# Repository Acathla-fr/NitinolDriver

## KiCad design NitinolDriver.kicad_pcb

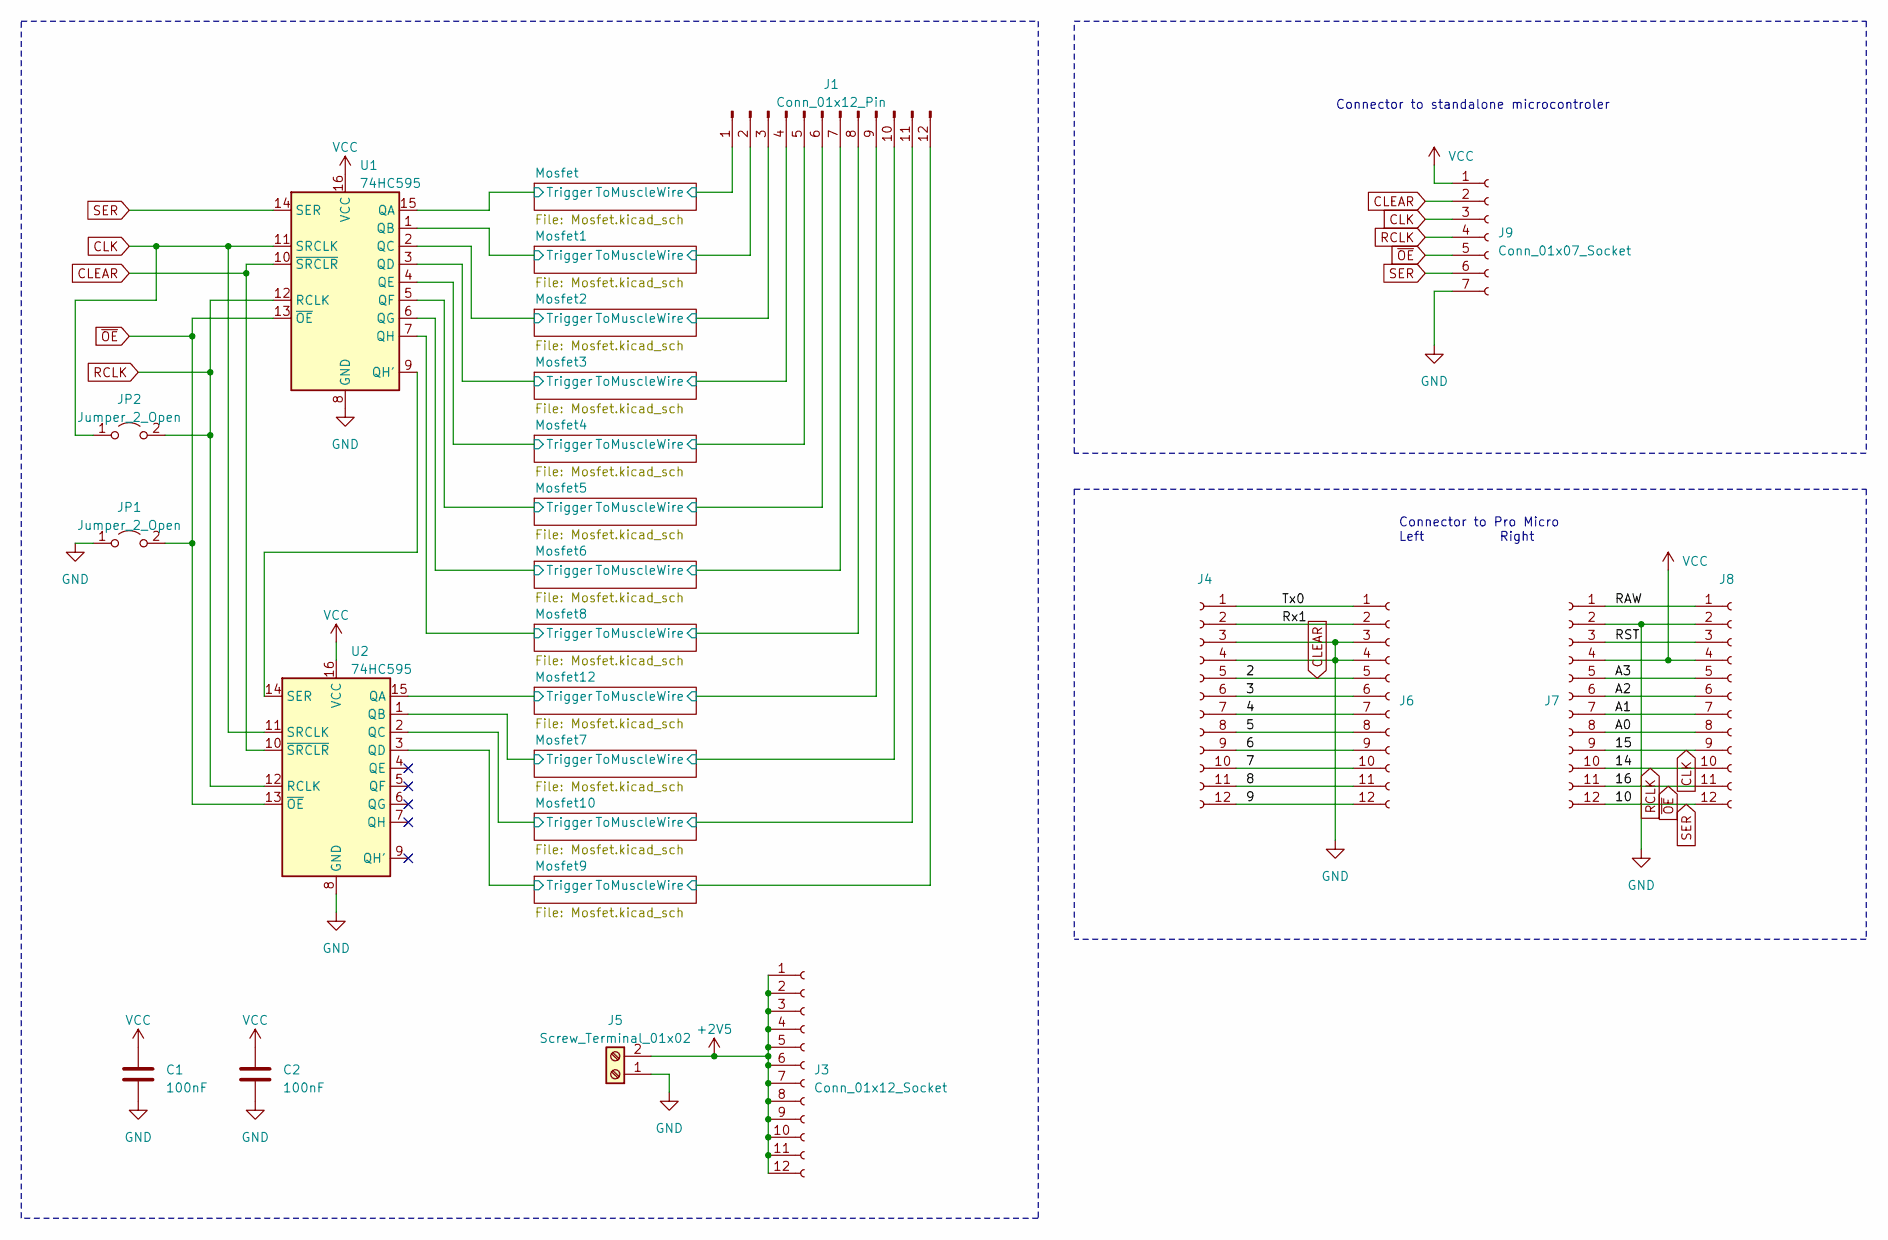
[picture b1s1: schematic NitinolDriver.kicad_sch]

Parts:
C1, C2: 100nF; C_0805_2012Metric_Pad1.18x1.45mm_HandSolder
J1: Conn_01x12_Pin; PinHeader_1x12_P2.54mm_Horizontal
J3: Conn_01x12_Socket; PinSocket_1x12_P2.54mm_Horizontal
J4, J6, J7, J8: Conn_01x12_Socket; PinSocket_1x12_P2.54mm_Vertical
J5: Screw_Terminal_01x02; TerminalBlock_bornier-2_P5.08mm
J9: Conn_01x07_Socket; PinSocket_1x07_P2.54mm_Horizontal
JP1, JP2: Jumper_2_Open; PinHeader_1x02_P2.54mm_Horizontal
U1, U2: 74HC595; SOIC-16_3.9x9.9mm_P1.27mm

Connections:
+2V5: J3.1, J3.2, J3.3, J3.4, J3.5, J3.6, J3.7, J3.8, J3.9, J3.10, J3.11, J3.12, J5.2
/3: J4.6, J6.6
/4: J4.7, J6.7
/5: J4.8, J6.8
/6: J4.9, J6.9
/7: J4.10, J6.10
/8: J4.11, J6.11
/9: J4.12, J6.12
/A0: J7.8, J8.8
/A1: J7.7, J8.7
/A2: J7.6, J8.6
/A3: J7.5, J8.5
/Mosfet1/ToMuscleWire: J1.2; also elsewhere on the board
/Mosfet1/Trigger: U1.1 (QB); also elsewhere on the board
/Mosfet2/ToMuscleWire: J1.3; also elsewhere on the board
/Mosfet2/Trigger: U1.2 (QC); also elsewhere on the board
/Mosfet3/ToMuscleWire: J1.4; also elsewhere on the board
/Mosfet3/Trigger: U1.3 (QD); also elsewhere on the board
/Mosfet4/ToMuscleWire: J1.5; also elsewhere on the board
/Mosfet4/Trigger: U1.4 (QE); also elsewhere on the board
/Mosfet5/ToMuscleWire: J1.6; also elsewhere on the board
/Mosfet5/Trigger: U1.5 (QF); also elsewhere on the board
/Mosfet6/ToMuscleWire: J1.7; also elsewhere on the board
/Mosfet6/Trigger: U1.6 (QG); also elsewhere on the board
/Mosfet7/ToMuscleWire: J1.10; also elsewhere on the board
/Mosfet7/Trigger: U2.1 (QB); also elsewhere on the board
/Mosfet8/ToMuscleWire: J1.8; also elsewhere on the board
/Mosfet8/Trigger: U1.7 (QH); also elsewhere on the board
/Mosfet9/ToMuscleWire: J1.12; also elsewhere on the board
/Mosfet9/Trigger: U2.3 (QD); also elsewhere on the board
/Mosfet10/ToMuscleWire: J1.11; also elsewhere on the board
/Mosfet10/Trigger: U2.2 (QC); also elsewhere on the board
/Mosfet12/ToMuscleWire: J1.9; also elsewhere on the board
/Mosfet12/Trigger: U2.15 (QA); also elsewhere on the board
/Mosfet/ToMuscleWire: J1.1; also elsewhere on the board
/Mosfet/Trigger: U1.15 (QA); also elsewhere on the board
/RAW: J7.1, J8.1
/RST: J7.3, J8.3
/Rx1: J4.2, J6.2
/Tx0: J4.1, J6.1
CLEAR: J4.5, J6.5, J9.2, U1.10 (~SRCLR), U2.10 (~SRCLR)
CLK: J7.9, J8.9, J9.3, JP2.1 (A), U1.11 (SRCLK), U2.11 (SRCLK)
GND: C1.2, C2.2, J4.3, J4.4, J5.1, J6.3, J6.4, J7.2, J8.2, J9.7, JP1.1 (A), U1.8 (GND), U2.8 (GND); also elsewhere on the board
unnamed: U1.9 (QH'), U2.14 (SER)
RCLK: J7.10, J8.10, J9.4, JP2.2 (B), U1.12 (RCLK), U2.12 (RCLK)
SER: J7.12, J8.12, J9.6, U1.14 (SER)
VCC: C1.1, C2.1, J7.4, J8.4, J9.1, U1.16 (VCC), U2.16 (VCC)
~OE: J7.11, J8.11, J9.5, JP1.2 (B), U1.13 (~OE), U2.13 (~OE)

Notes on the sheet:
Connector to Pro Micro Left Right
Connector to standalone microcontroler

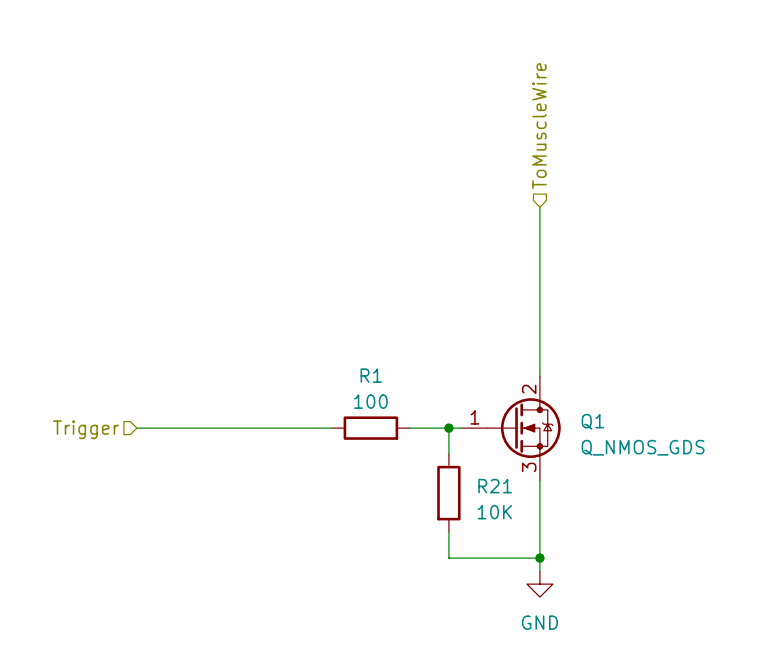
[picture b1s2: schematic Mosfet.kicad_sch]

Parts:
Q1: Q_NMOS_GDS; SOT-223-3_TabPin2
R1: 100; R_0805_2012Metric_Pad1.20x1.40mm_HandSolder
R21: 10K; R_0805_2012Metric_Pad1.20x1.40mm_HandSolder

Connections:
/Mosfet/ToMuscleWire: Q1.2 (D); also elsewhere on the board
/Mosfet/Trigger: R1.1; also elsewhere on the board
GND: Q1.3 (S), R21.2; also elsewhere on the board

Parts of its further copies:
Q2, Q3, Q4, Q5, Q6, Q7, Q8, Q9, Q10, Q11, Q12: Q_NMOS_GDS; SOT-223-3_TabPin2
R2, R3, R4, R5, R6, R7, R8, R9, R10, R11, R12: 100; R_0805_2012Metric_Pad1.20x1.40mm_HandSolder
R13, R14, R15, R16, R17, R18, R19, R20, R22, R23, R24: 10K; R_0805_2012Metric_Pad1.20x1.40mm_HandSolder

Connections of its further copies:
/Mosfet1/ToMuscleWire: Q2.2 (D); also elsewhere on the board
/Mosfet1/Trigger: R2.1; also elsewhere on the board
/Mosfet2/ToMuscleWire: Q3.2 (D); also elsewhere on the board
/Mosfet2/Trigger: R3.1; also elsewhere on the board
/Mosfet3/ToMuscleWire: Q4.2 (D); also elsewhere on the board
/Mosfet3/Trigger: R4.1; also elsewhere on the board
/Mosfet4/ToMuscleWire: Q5.2 (D); also elsewhere on the board
/Mosfet4/Trigger: R5.1; also elsewhere on the board
/Mosfet5/ToMuscleWire: Q6.2 (D); also elsewhere on the board
/Mosfet5/Trigger: R6.1; also elsewhere on the board
/Mosfet6/ToMuscleWire: Q7.2 (D); also elsewhere on the board
/Mosfet6/Trigger: R7.1; also elsewhere on the board
/Mosfet7/ToMuscleWire: Q10.2 (D); also elsewhere on the board
/Mosfet7/Trigger: R10.1; also elsewhere on the board
/Mosfet8/ToMuscleWire: Q8.2 (D); also elsewhere on the board
/Mosfet8/Trigger: R8.1; also elsewhere on the board
/Mosfet9/ToMuscleWire: Q12.2 (D); also elsewhere on the board
/Mosfet9/Trigger: R12.1; also elsewhere on the board
/Mosfet10/ToMuscleWire: Q11.2 (D); also elsewhere on the board
/Mosfet10/Trigger: R11.1; also elsewhere on the board
/Mosfet12/ToMuscleWire: Q9.2 (D); also elsewhere on the board
/Mosfet12/Trigger: R9.1; also elsewhere on the board
GND: Q2.3 (S), Q3.3 (S), Q4.3 (S), Q5.3 (S), Q6.3 (S), Q7.3 (S), Q8.3 (S), Q9.3 (S), Q10.3 (S), Q11.3 (S), Q12.3 (S), R13.2, R14.2, R15.2, R16.2, R17.2, R18.2, R19.2, R20.2, R22.2, R23.2, R24.2; also elsewhere on the board
unnamed: Q2.1 (G), R2.2, R14.1
unnamed: Q3.1 (G), R3.2, R15.1
unnamed: Q4.1 (G), R4.2, R16.1
unnamed: Q5.1 (G), R5.2, R17.1
unnamed: Q6.1 (G), R6.2, R18.1
unnamed: Q7.1 (G), R7.2, R19.1
unnamed: Q8.1 (G), R8.2, R20.1
unnamed: Q10.1 (G), R10.2, R22.1
unnamed: Q11.1 (G), R11.2, R23.1
unnamed: Q12.1 (G), R12.2, R24.1

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
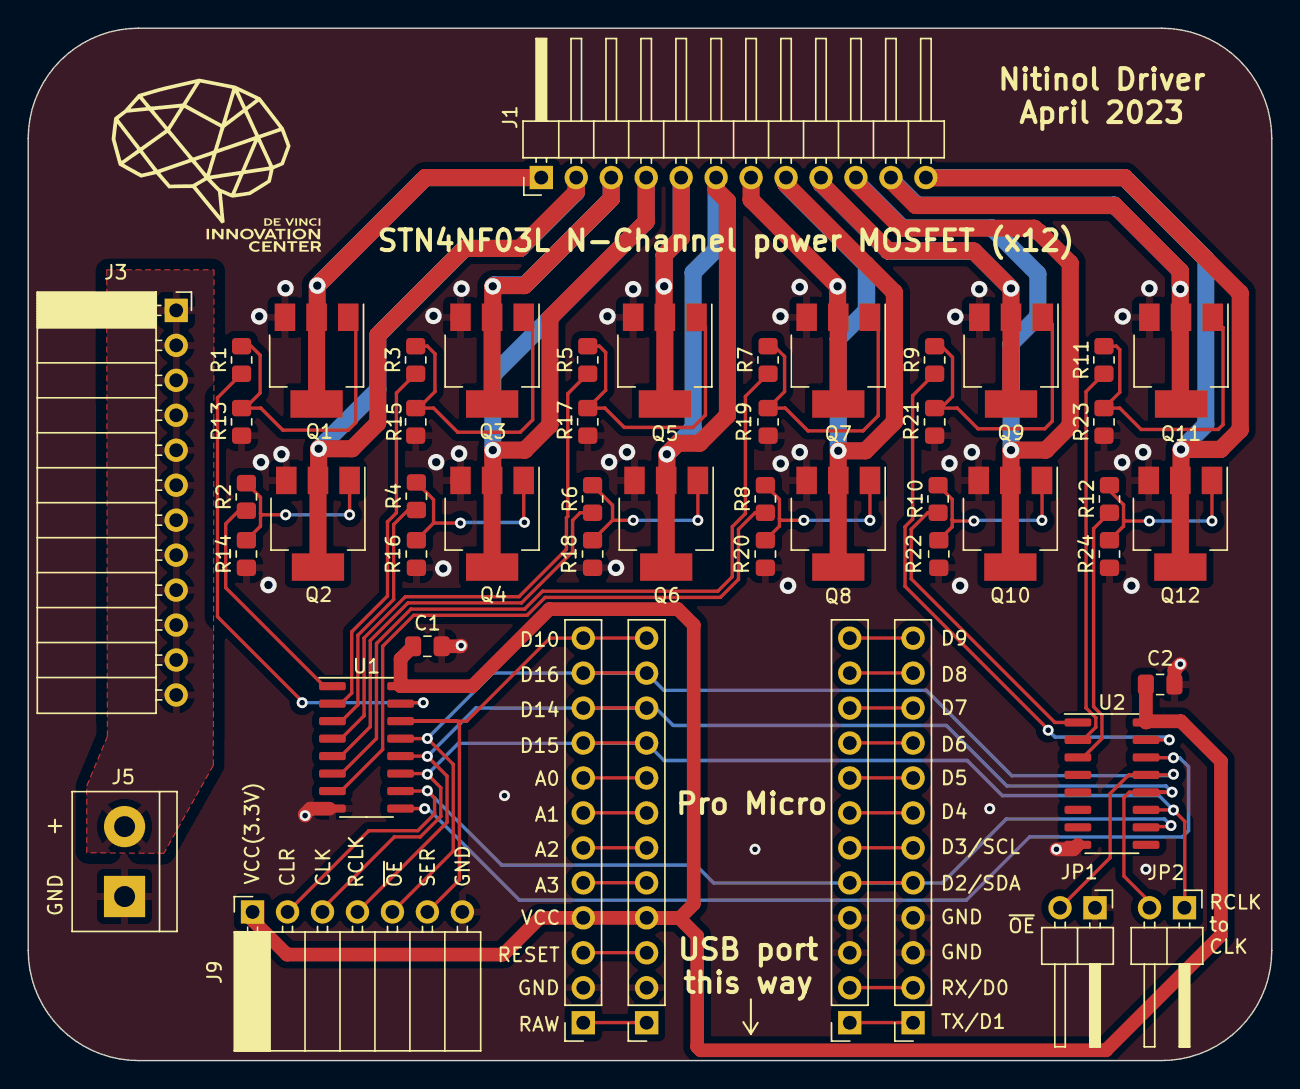
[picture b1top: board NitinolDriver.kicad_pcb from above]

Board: 2 copper layers, 90.3 x 75.0 mm, 50 parts (0 on the bottom side), 60 nets.

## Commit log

2023-10-26 Arduino code
2023-10-26 Kicad files
